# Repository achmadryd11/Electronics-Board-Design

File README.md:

# Electronics-Board-Design
PCB (Printed Circuit Board)

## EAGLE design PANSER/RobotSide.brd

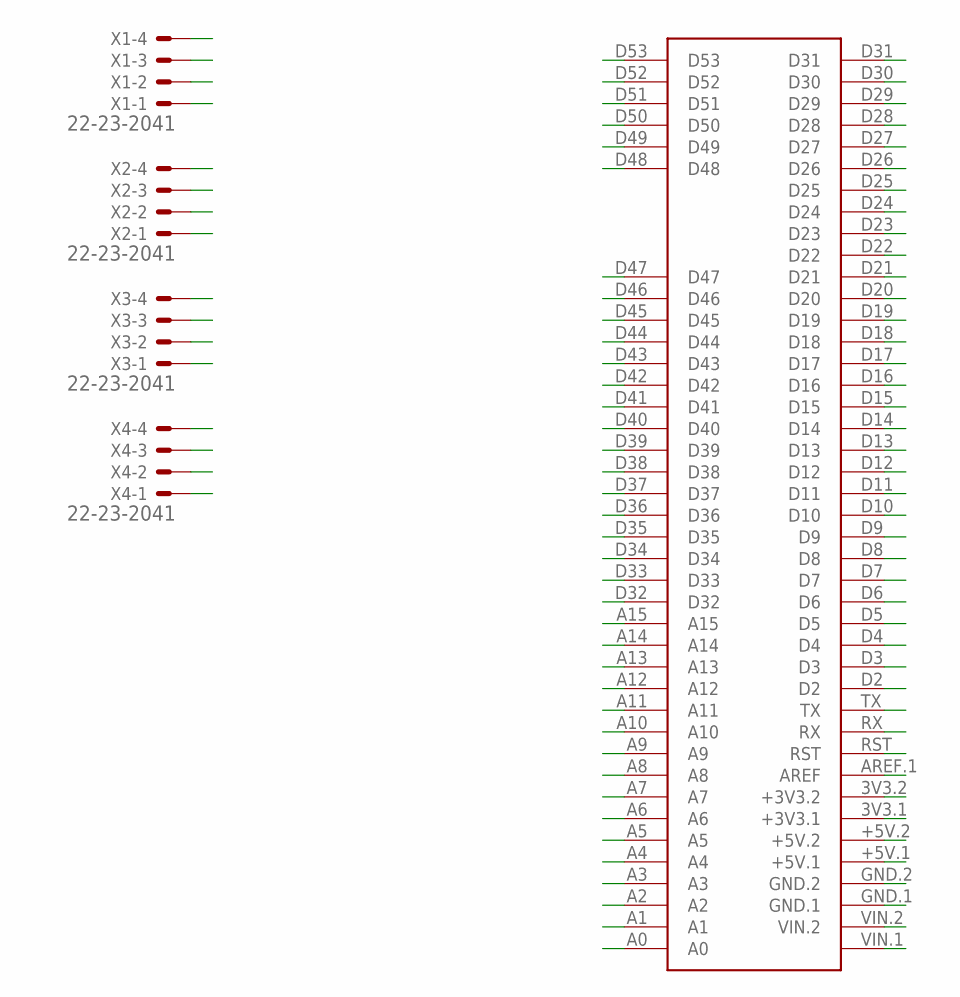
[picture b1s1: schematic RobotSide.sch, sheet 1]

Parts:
U$1: MEGA2560_MIKRO
X1, X2, X3, X4: 22-23-2041

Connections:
3V3: U$1.3V3.1 (+3V3.1), U$1.3V3.2 (+3V3.2)
5V: U$1.+5V.1, U$1.+5V.2; also elsewhere on the board
A0: U$1.A0
A1: U$1.A1
A2: U$1.A2
A3: U$1.A3
A4: U$1.A4
A5: U$1.A5
A6: U$1.A6
A7: U$1.A7
A8: U$1.A8
A9: U$1.A9
A10: U$1.A10
A11: U$1.A11
A12: U$1.A12
A13: U$1.A13
A14: U$1.A14
A15: U$1.A15
AREF: U$1.AREF.1 (AREF)
D2: U$1.D2
D3: U$1.D3
D4: U$1.D4
D5: U$1.D5
D6: U$1.D6
D7: U$1.D7
D8: U$1.D8
D9: U$1.D9
D10: U$1.D10
D11: U$1.D11
D12: U$1.D12
D13: U$1.D13
D14: U$1.D14
D15: U$1.D15
D16: U$1.D16
D17: U$1.D17
D18: U$1.D18
D19: U$1.D19
D20: U$1.D20
D21: U$1.D21
D22: U$1.D22
D23: U$1.D23
D24: U$1.D24
D25: U$1.D25
D26: U$1.D26
D27: U$1.D27
D28: U$1.D28
D29: U$1.D29
D30: U$1.D30
D31: U$1.D31
D32: U$1.D32
D33: U$1.D33
D34: U$1.D34
D35: U$1.D35
D36: U$1.D36
D37: U$1.D37
D38: U$1.D38
D39: U$1.D39
D40: U$1.D40
D41: U$1.D41
D42: U$1.D42
D43: U$1.D43
D44: U$1.D44
D45: U$1.D45
D46: U$1.D46
D47: U$1.D47
D49: U$1.D49
D50: U$1.D50
D51: U$1.D51
D52: U$1.D52
D53: U$1.D53
GND: U$1.GND.1, U$1.GND.2; also elsewhere on the board
RST: U$1.RST
RX0: U$1.RX
TX0: U$1.TX
VIN: U$1.VIN.1, U$1.VIN.2

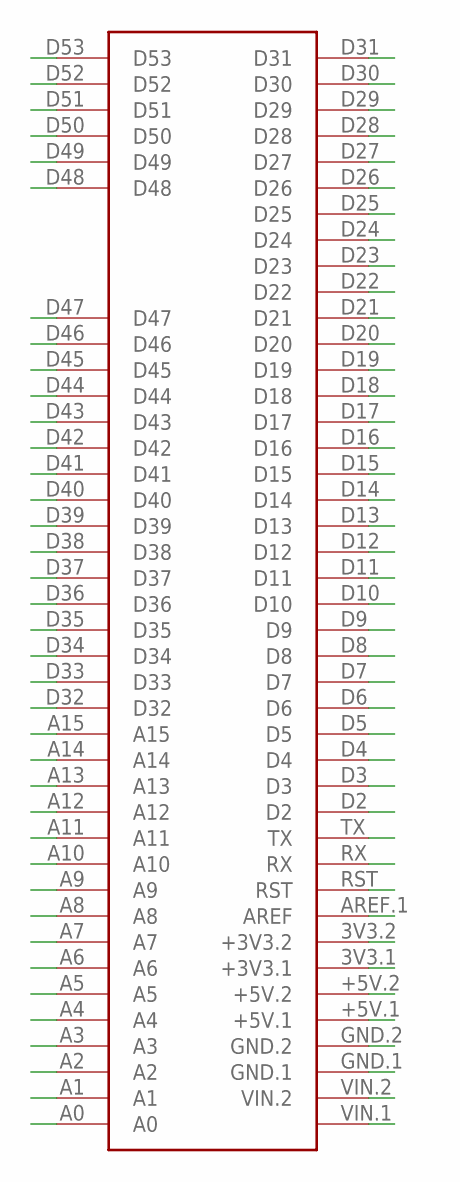
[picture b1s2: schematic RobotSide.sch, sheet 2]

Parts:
U$2: MEGA2560_MIKRO

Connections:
3V3_A: U$2.3V3.1 (+3V3.1), U$2.3V3.2 (+3V3.2)
5V: U$2.+5V.1, U$2.+5V.2; also elsewhere on the board
A0_A: U$2.A0
A1_A: U$2.A1
A2_A: U$2.A2
A3_A: U$2.A3
A4_A: U$2.A4
A5_A: U$2.A5
A6_A: U$2.A6
A7_A: U$2.A7
A8_A: U$2.A8
A9_A: U$2.A9
A10_A: U$2.A10
A11_A: U$2.A11
A12_A: U$2.A12
A13_A: U$2.A13
A14_A: U$2.A14
A15_A: U$2.A15
AREF_A: U$2.AREF.1 (AREF)
D2_A: U$2.D2
D3_A: U$2.D3
D4_A: U$2.D4
D5_A: U$2.D5
D6_A: U$2.D6
D7_A: U$2.D7
D8_A: U$2.D8
D9_A: U$2.D9
D10_A: U$2.D10
D11_A: U$2.D11
D12_A: U$2.D12
D13_A: U$2.D13
D14_A: U$2.D14
D15_A: U$2.D15
D16_A: U$2.D16
D17_A: U$2.D17
D18_A: U$2.D18
D19_A: U$2.D19
D20_A: U$2.D20
D21_A: U$2.D21
D22_A: U$2.D22
D23_A: U$2.D23
D24_A: U$2.D24
D25_A: U$2.D25
D26_A: U$2.D26
D27_A: U$2.D27
D28_A: U$2.D28
D29_A: U$2.D29
D30_A: U$2.D30
D31_A: U$2.D31
D32_A: U$2.D32
D33_A: U$2.D33
D34_A: U$2.D34
D35_A: U$2.D35
D36_A: U$2.D36
D37_A: U$2.D37
D38_A: U$2.D38
D39_A: U$2.D39
D40_A: U$2.D40
D41_A: U$2.D41
D42_A: U$2.D42
D43_A: U$2.D43
D44_A: U$2.D44
D45_A: U$2.D45
D46_A: U$2.D46
D47_A: U$2.D47
D48_A: U$2.D48
D49_A: U$2.D49
D50_A: U$2.D50
D51_A: U$2.D51
D52_A: U$2.D52
D53_A: U$2.D53
GND: U$2.GND.1, U$2.GND.2; also elsewhere on the board
RST_A: U$2.RST
RX0_A: U$2.RX
TX0_A: U$2.TX
VIN_A: U$2.VIN.1, U$2.VIN.2

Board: 2 copper layers, 6 parts (0 on the bottom side), 6 nets, no tracks yet.

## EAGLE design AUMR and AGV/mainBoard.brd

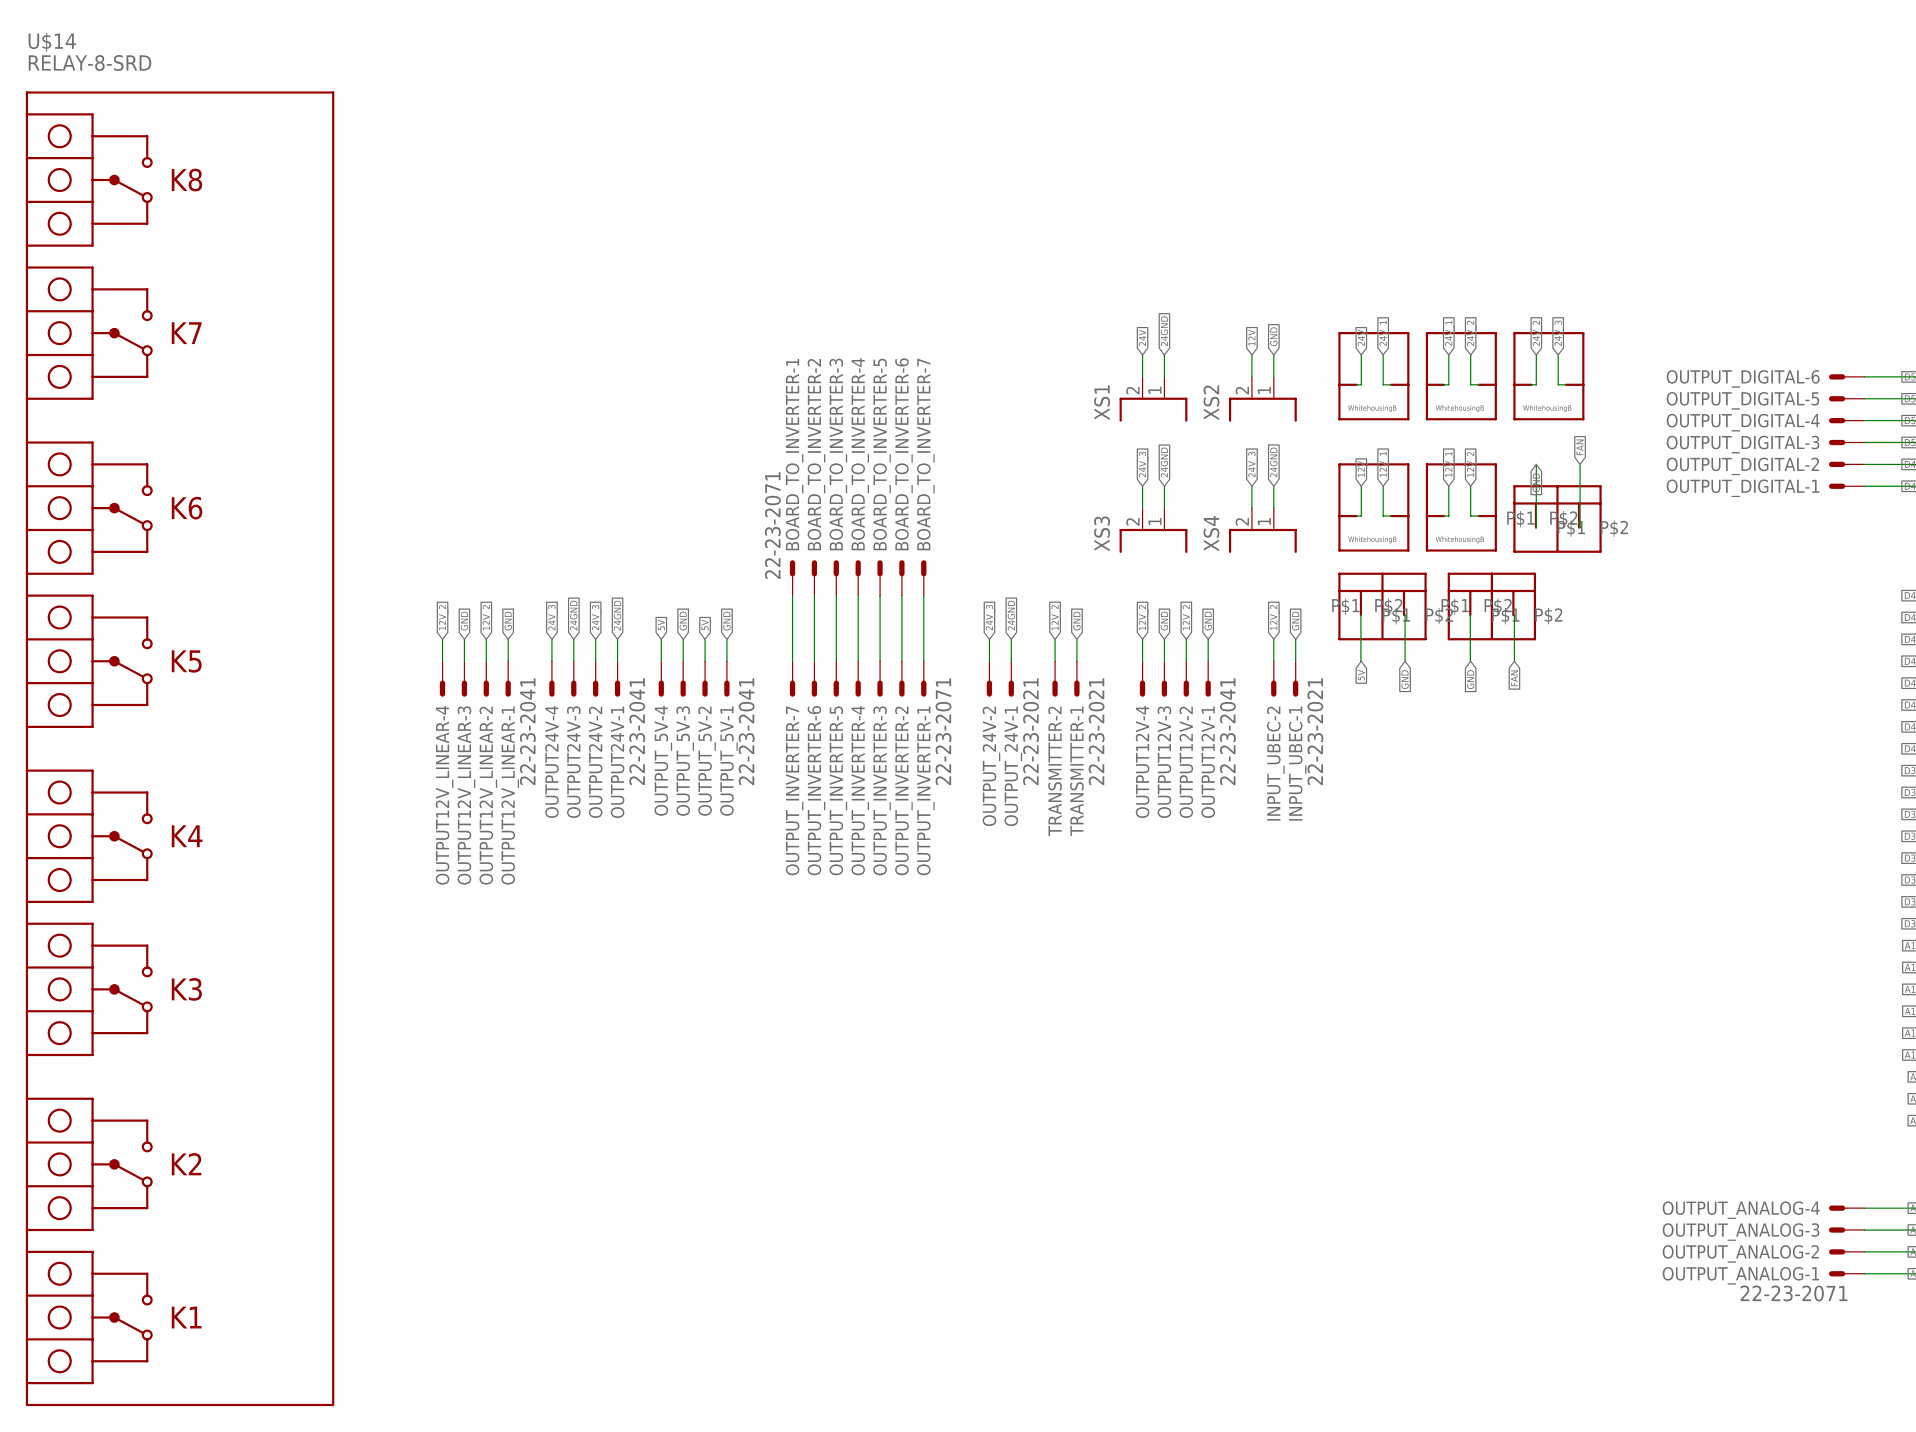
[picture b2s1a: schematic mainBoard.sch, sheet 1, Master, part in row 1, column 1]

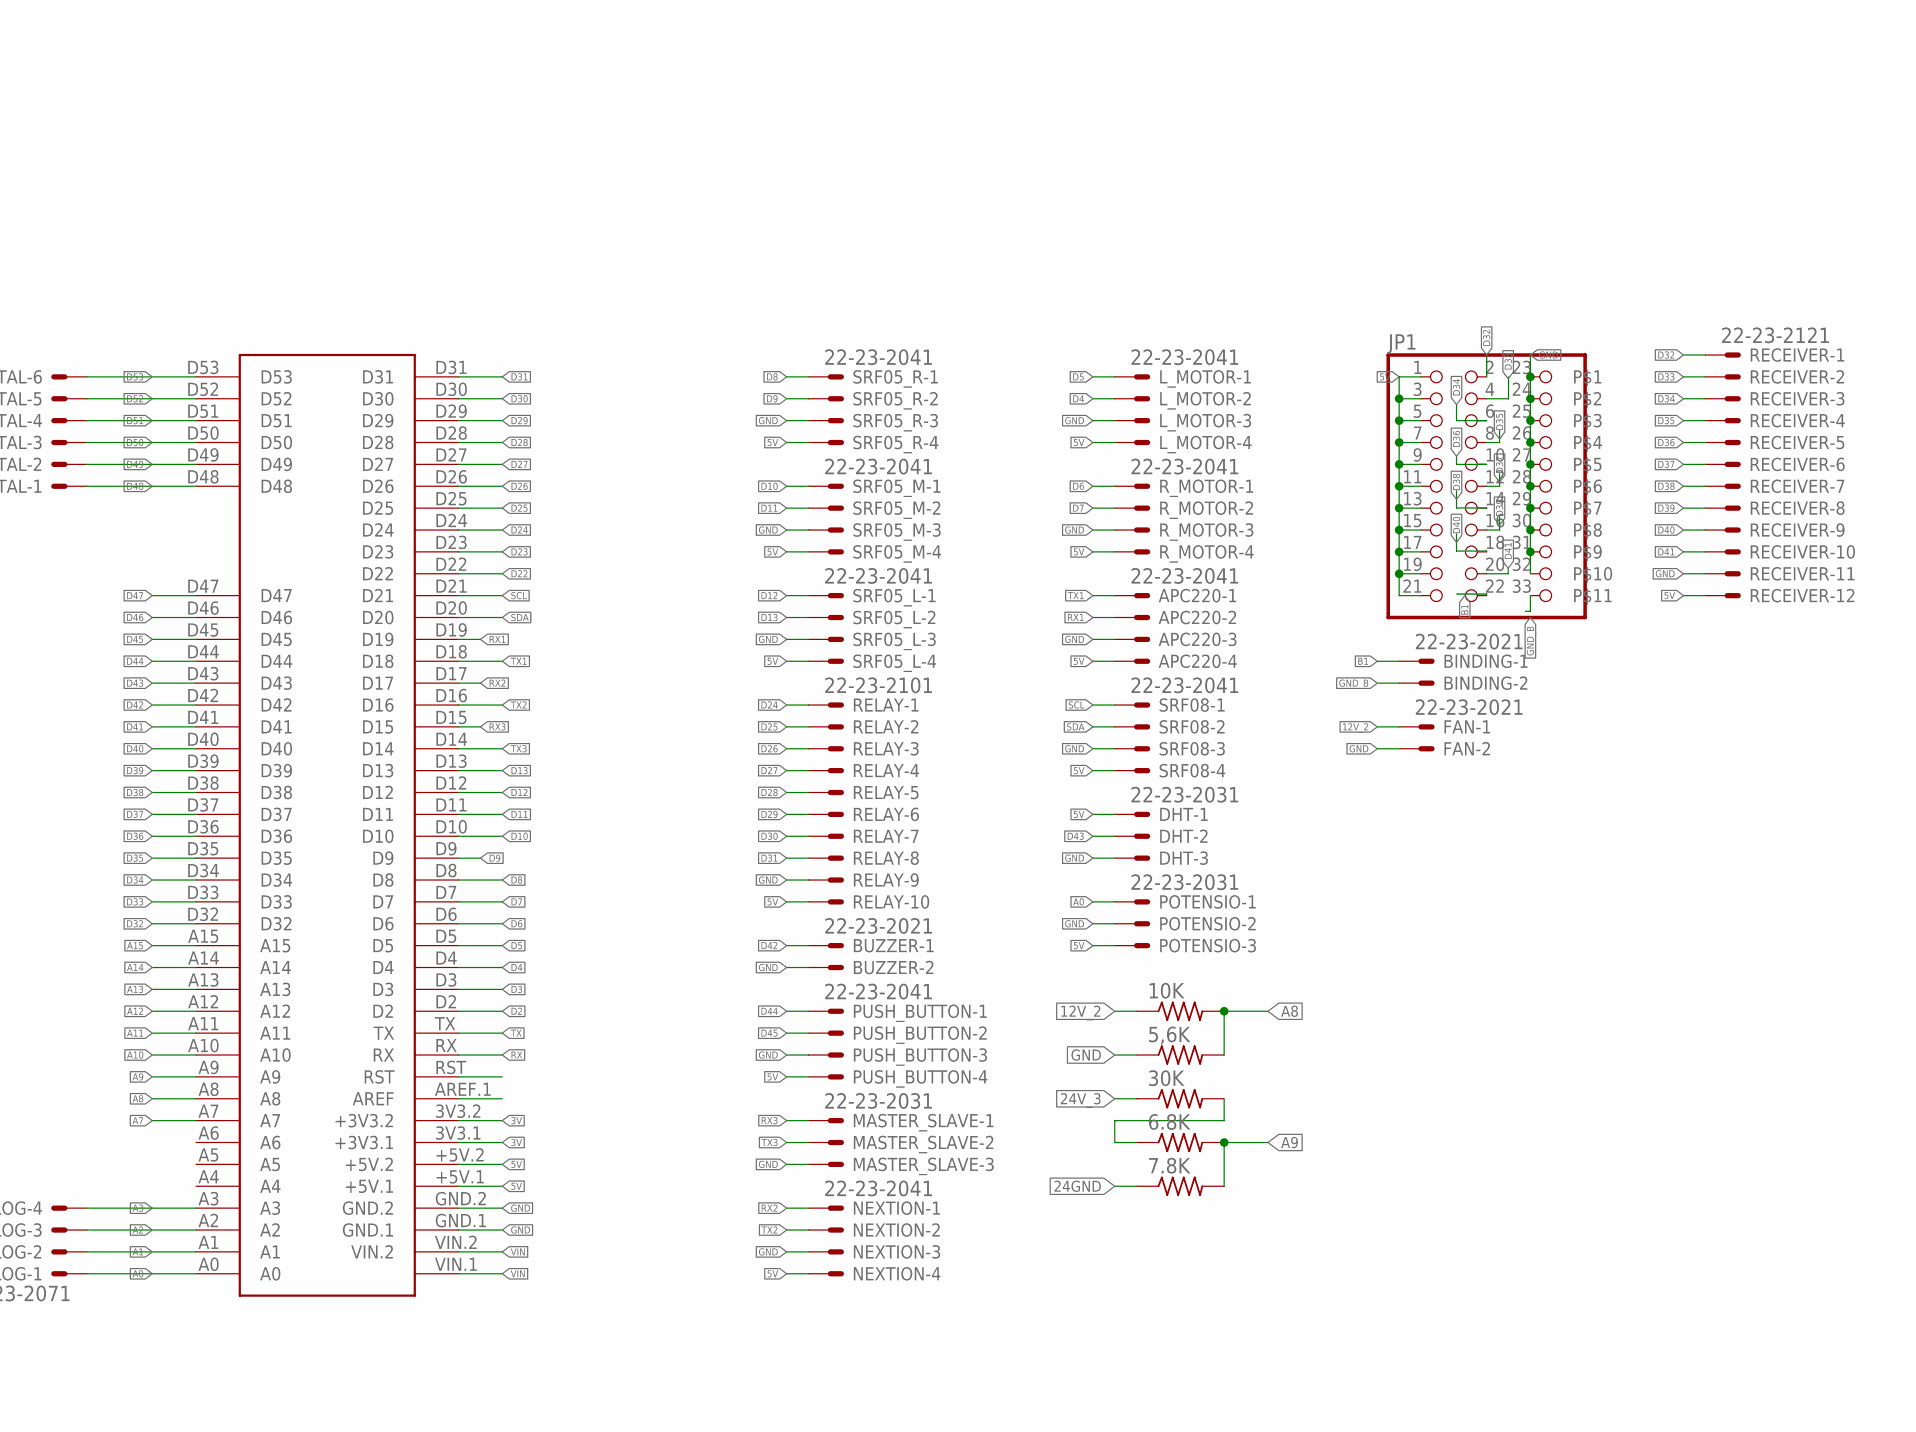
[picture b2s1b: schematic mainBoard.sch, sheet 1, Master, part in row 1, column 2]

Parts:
5,6K, 6.8K, 7.8K, 10K, 30K: R-US_0207/7; 0207/7
APC220: 22-23-2041
BINDING: 22-23-2021
BOARD_TO_INVERTER: 22-23-2071
BUZZER: 22-23-2021
DHT: 22-23-2031
EMERGENCY: WHB
FAN: 22-23-2021
FANLEFT: TERMINALBLOCK5MM
FANRIGHT: TERMINALBLOCK5MM
FUSE12V, FUSE24V: WHB
INPUT_UBEC: 22-23-2021
JP1: PINHD-2X11; 2X11
L_MOTOR: 22-23-2041
MASTER_SLAVE: 22-23-2031
NEXTION: 22-23-2041
OUTPUT12V, OUTPUT12V_LINEAR, OUTPUT24V: 22-23-2041
OUTPUT_5V: 22-23-2041
OUTPUT_24V: 22-23-2021
OUTPUT_ANALOG: 22-23-2071
OUTPUT_DIGITAL: 22-23-2061
OUTPUT_INVERTER: 22-23-2071
POTENSIO: 22-23-2031
PUSH_BUTTON: 22-23-2041
RECEIVER: 22-23-2121
RELAY: 22-23-2101
R_MOTOR: 22-23-2041
SRF05_L, SRF05_M, SRF05_R, SRF08: 22-23-2041
SWITCH24V: WHB
SWTICH12V: WHB
TRANSMITTER: 22-23-2021
U$1: MEGA2560_MIKRO
U$14: RELAY-8-SRD
UBEC_OUTPUT: TERMINALBLOCK5MM
XS1, XS2, XS3, XS4: 2P; DG55CB-2P-1

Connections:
3V: U$1.3V3.1 (+3V3.1), U$1.3V3.2 (+3V3.2); also elsewhere on the board
5V: APC220.4, DHT.1, JP1.1, JP1.3, JP1.5, JP1.7, JP1.9, JP1.11, JP1.13, JP1.15, JP1.17, JP1.19, JP1.21, L_MOTOR.4, NEXTION.4, OUTPUT_5V.2, OUTPUT_5V.4, POTENSIO.3, PUSH_BUTTON.4, RECEIVER.12, RELAY.10, R_MOTOR.4, SRF05_L.4, SRF05_M.4, SRF05_R.4, SRF08.4, U$1.+5V.1, U$1.+5V.2, UBEC_OUTPUT.P$1; also elsewhere on the board
12V: FUSE12V.P$1, XS2.2
12V_1: FUSE12V.P$2, SWTICH12V.P$1
12V_2: 10K.1, FAN.1, INPUT_UBEC.2, OUTPUT12V.2, OUTPUT12V.4, OUTPUT12V_LINEAR.2, OUTPUT12V_LINEAR.4, SWTICH12V.P$2, TRANSMITTER.2; also elsewhere on the board
24GND: 7.8K.1, OUTPUT24V.1, OUTPUT24V.3, OUTPUT_24V.1, XS1.1, XS3.1, XS4.1
24V: FUSE24V.P$1, XS1.2
24V_1: FUSE24V.P$2, SWITCH24V.P$1
24V_2: EMERGENCY.P$1, SWITCH24V.P$2
24V_3: 30K.1, EMERGENCY.P$2, OUTPUT24V.2, OUTPUT24V.4, OUTPUT_24V.2, XS3.2, XS4.2
A0: OUTPUT_ANALOG.1, POTENSIO.1, U$1.A0
A1: OUTPUT_ANALOG.2, U$1.A1
A2: OUTPUT_ANALOG.3, U$1.A2
A3: OUTPUT_ANALOG.4, U$1.A3
A7: U$1.A7
A8: 5,6K.2, 10K.2, U$1.A8
A9: 6.8K.2, 7.8K.2, U$1.A9
A10: U$1.A10
A11: U$1.A11
A12: U$1.A12
A13: U$1.A13
A14: U$1.A14
A15: U$1.A15
B1: BINDING.1, JP1.22
D2: U$1.D2
D3: U$1.D3
D4: L_MOTOR.2, U$1.D4
D5: L_MOTOR.1, U$1.D5
D6: R_MOTOR.1, U$1.D6
D7: R_MOTOR.2, U$1.D7
D8: SRF05_R.1, U$1.D8
D9: SRF05_R.2, U$1.D9
D10: SRF05_M.1, U$1.D10
D11: SRF05_M.2, U$1.D11
D12: SRF05_L.1, U$1.D12
D13: SRF05_L.2, U$1.D13
D22: U$1.D22
D23: U$1.D23
D24: RELAY.1, U$1.D24
D25: RELAY.2, U$1.D25
D26: RELAY.3, U$1.D26
D27: RELAY.4, U$1.D27
D28: RELAY.5, U$1.D28
D29: RELAY.6, U$1.D29
D30: RELAY.7, U$1.D30
D31: RELAY.8, U$1.D31
D32: JP1.2, RECEIVER.1, U$1.D32
D33: JP1.4, RECEIVER.2, U$1.D33
D34: JP1.6, RECEIVER.3, U$1.D34
D35: JP1.8, RECEIVER.4, U$1.D35
D36: JP1.10, RECEIVER.5, U$1.D36
D37: JP1.12, RECEIVER.6, U$1.D37
D38: JP1.14, RECEIVER.7, U$1.D38
D39: JP1.16, RECEIVER.8, U$1.D39
D40: JP1.18, RECEIVER.9, U$1.D40
D41: JP1.20, RECEIVER.10, U$1.D41
D42: BUZZER.1, U$1.D42
D43: DHT.2, U$1.D43
D44: PUSH_BUTTON.1, U$1.D44
D45: PUSH_BUTTON.2, U$1.D45
D46: U$1.D46
D47: U$1.D47
D48: OUTPUT_DIGITAL.1, U$1.D48
D49: OUTPUT_DIGITAL.2, U$1.D49
D50: OUTPUT_DIGITAL.3, U$1.D50
D51: OUTPUT_DIGITAL.4, U$1.D51
D52: OUTPUT_DIGITAL.5, U$1.D52
D53: OUTPUT_DIGITAL.6, U$1.D53
FAN: FANLEFT.P$2, FANRIGHT.P$2
GND: 5,6K.1, APC220.3, BUZZER.2, DHT.3, FAN.2, FANLEFT.P$1, FANRIGHT.P$1, INPUT_UBEC.1, JP1.23, JP1.24, JP1.25, JP1.26, JP1.27, JP1.28, JP1.29, JP1.30, JP1.31, JP1.32, L_MOTOR.3, MASTER_SLAVE.3, NEXTION.3, OUTPUT12V.1, OUTPUT12V.3, OUTPUT12V_LINEAR.1, OUTPUT12V_LINEAR.3, OUTPUT_5V.1, OUTPUT_5V.3, POTENSIO.2, PUSH_BUTTON.3, RECEIVER.11, RELAY.9, R_MOTOR.3, SRF05_L.3, SRF05_M.3, SRF05_R.3, SRF08.3, TRANSMITTER.1, U$1.GND.1, U$1.GND.2, UBEC_OUTPUT.P$2, XS2.1; also elsewhere on the board
GND_B: BINDING.2, JP1.33
unnamed: 6.8K.1, 30K.2
unnamed: BOARD_TO_INVERTER.1, OUTPUT_INVERTER.7
unnamed: BOARD_TO_INVERTER.2, OUTPUT_INVERTER.6
unnamed: BOARD_TO_INVERTER.3, OUTPUT_INVERTER.5
unnamed: BOARD_TO_INVERTER.4, OUTPUT_INVERTER.4
unnamed: BOARD_TO_INVERTER.5, OUTPUT_INVERTER.3
unnamed: BOARD_TO_INVERTER.6, OUTPUT_INVERTER.2
unnamed: BOARD_TO_INVERTER.7, OUTPUT_INVERTER.1
RX: U$1.RX
RX1: APC220.2, U$1.D19
RX2: NEXTION.1, U$1.D17
RX3: MASTER_SLAVE.1, U$1.D15; also elsewhere on the board
SCL: SRF08.1, U$1.D21
SDA: SRF08.2, U$1.D20
TX: U$1.TX
TX1: APC220.1, U$1.D18
TX2: NEXTION.2, U$1.D16
TX3: MASTER_SLAVE.2, U$1.D14; also elsewhere on the board
VIN: U$1.VIN.1, U$1.VIN.2; also elsewhere on the board

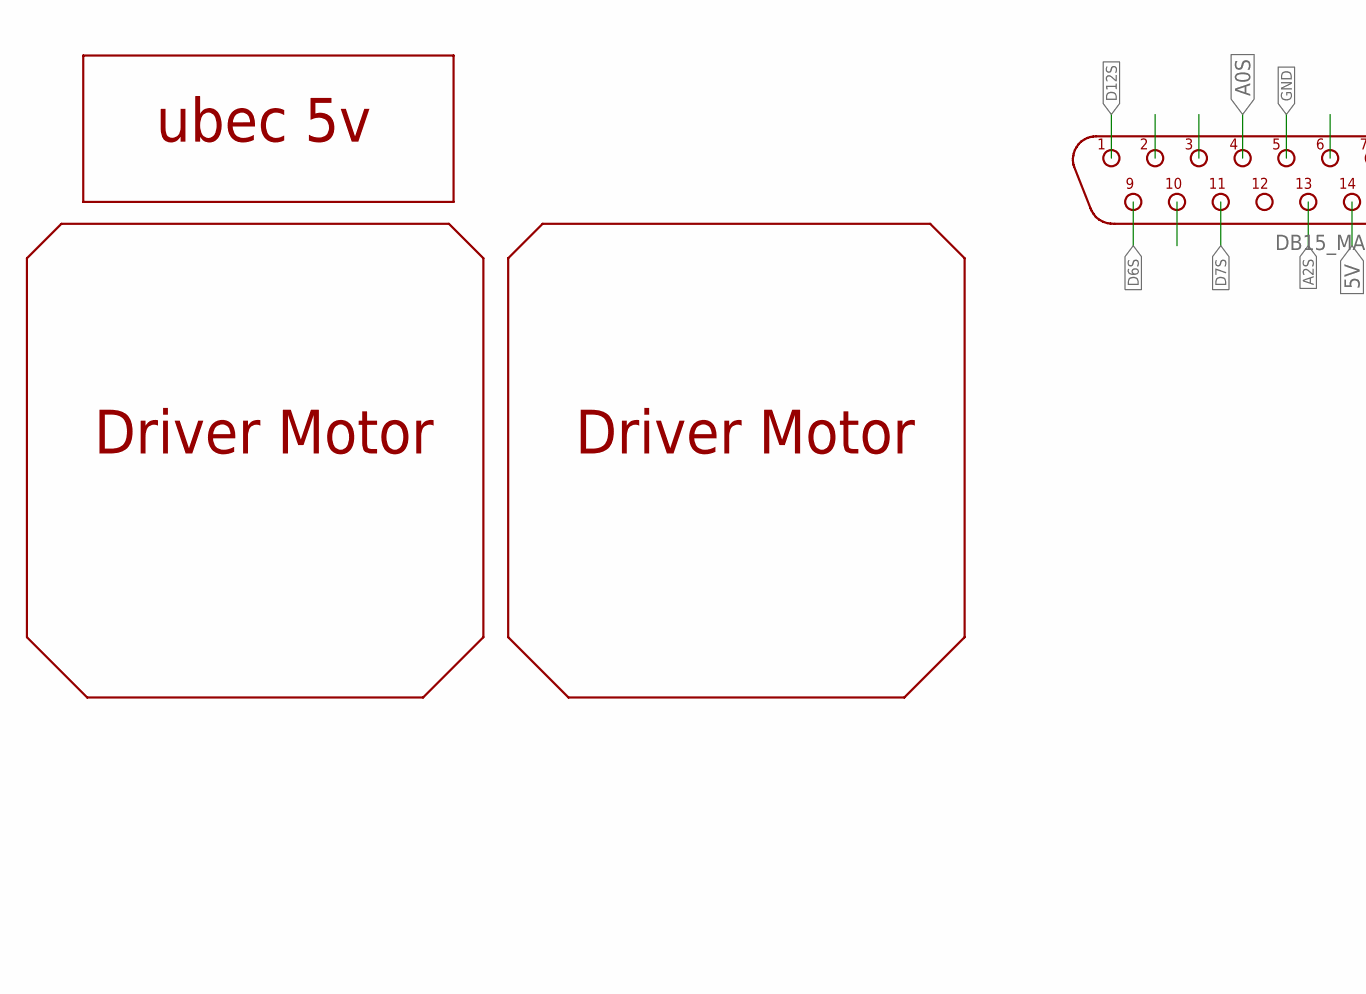
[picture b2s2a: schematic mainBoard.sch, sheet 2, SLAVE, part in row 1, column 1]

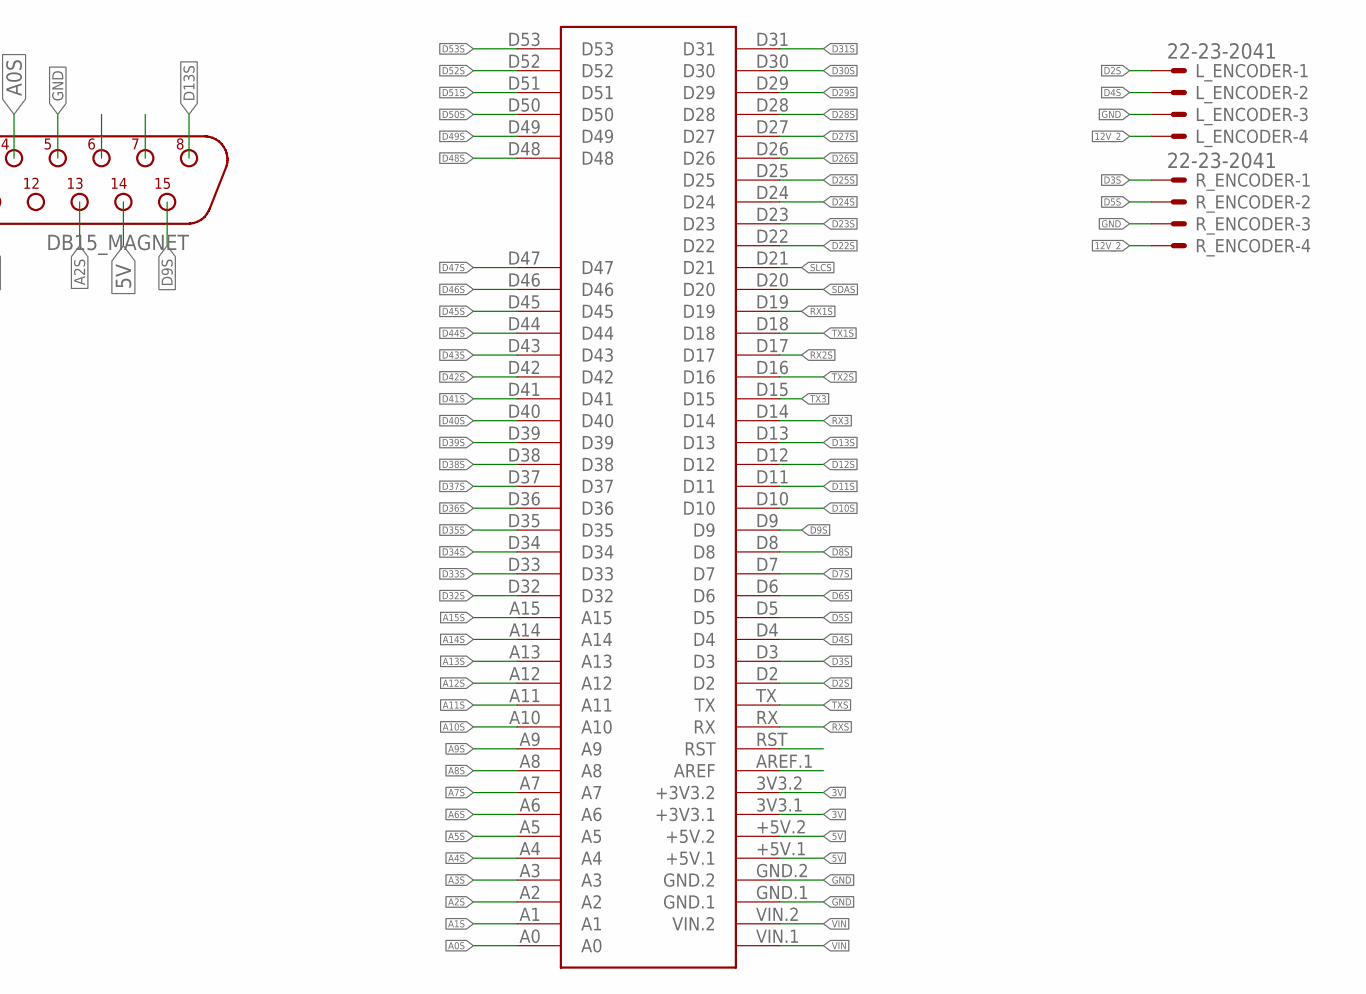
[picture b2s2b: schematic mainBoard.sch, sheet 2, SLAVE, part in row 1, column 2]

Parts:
DB15_MAGNET: DB15M/90; D-15M/90
L_ENCODER: 22-23-2041
R_ENCODER: 22-23-2041
U$2: MEGA2560_MIKRO
U$11, U$12: BT2; IBT2
U$13: UBEC; AD

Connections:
3V: U$2.3V3.1 (+3V3.1), U$2.3V3.2 (+3V3.2); also elsewhere on the board
5V: DB15_MAGNET.14, U$2.+5V.1, U$2.+5V.2; also elsewhere on the board
12V_2: L_ENCODER.4, R_ENCODER.4; also elsewhere on the board
A0S: DB15_MAGNET.4, U$2.A0
A1S: U$2.A1
A2S: DB15_MAGNET.13, U$2.A2
A3S: U$2.A3
A4S: U$2.A4
A5S: U$2.A5
A6S: U$2.A6
A7S: U$2.A7
A8S: U$2.A8
A9S: U$2.A9
A10S: U$2.A10
A11S: U$2.A11
A12S: U$2.A12
A13S: U$2.A13
A14S: U$2.A14
A15S: U$2.A15
D2S: L_ENCODER.1, U$2.D2
D3S: R_ENCODER.1, U$2.D3
D4S: L_ENCODER.2, U$2.D4
D5S: R_ENCODER.2, U$2.D5
D6S: DB15_MAGNET.9, U$2.D6
D7S: DB15_MAGNET.11, U$2.D7
D8S: U$2.D8
D9S: DB15_MAGNET.15, U$2.D9
D10S: U$2.D10
D11S: U$2.D11
D12S: DB15_MAGNET.1, U$2.D12
D13S: DB15_MAGNET.8, U$2.D13
D22S: U$2.D22
D23S: U$2.D23
D24S: U$2.D24
D25S: U$2.D25
D26S: U$2.D26
D27S: U$2.D27
D28S: U$2.D28
D29S: U$2.D29
D30S: U$2.D30
D31S: U$2.D31
D32S: U$2.D32
D33S: U$2.D33
D34S: U$2.D34
D35S: U$2.D35
D36S: U$2.D36
D37S: U$2.D37
D38S: U$2.D38
D39S: U$2.D39
D40S: U$2.D40
D41S: U$2.D41
D42S: U$2.D42
D43S: U$2.D43
D44S: U$2.D44
D45S: U$2.D45
D46S: U$2.D46
D47S: U$2.D47
D48S: U$2.D48
D49S: U$2.D49
D50S: U$2.D50
D51S: U$2.D51
D52S: U$2.D52
D53S: U$2.D53
GND: DB15_MAGNET.5, L_ENCODER.3, R_ENCODER.3, U$2.GND.1, U$2.GND.2; also elsewhere on the board
RX1S: U$2.D19
RX2S: U$2.D17
RX3: U$2.D14; also elsewhere on the board
RXS: U$2.RX
SDAS: U$2.D20
SLCS: U$2.D21
TX1S: U$2.D18
TX2S: U$2.D16
TX3: U$2.D15; also elsewhere on the board
TXS: U$2.TX
VIN: U$2.VIN.1, U$2.VIN.2; also elsewhere on the board

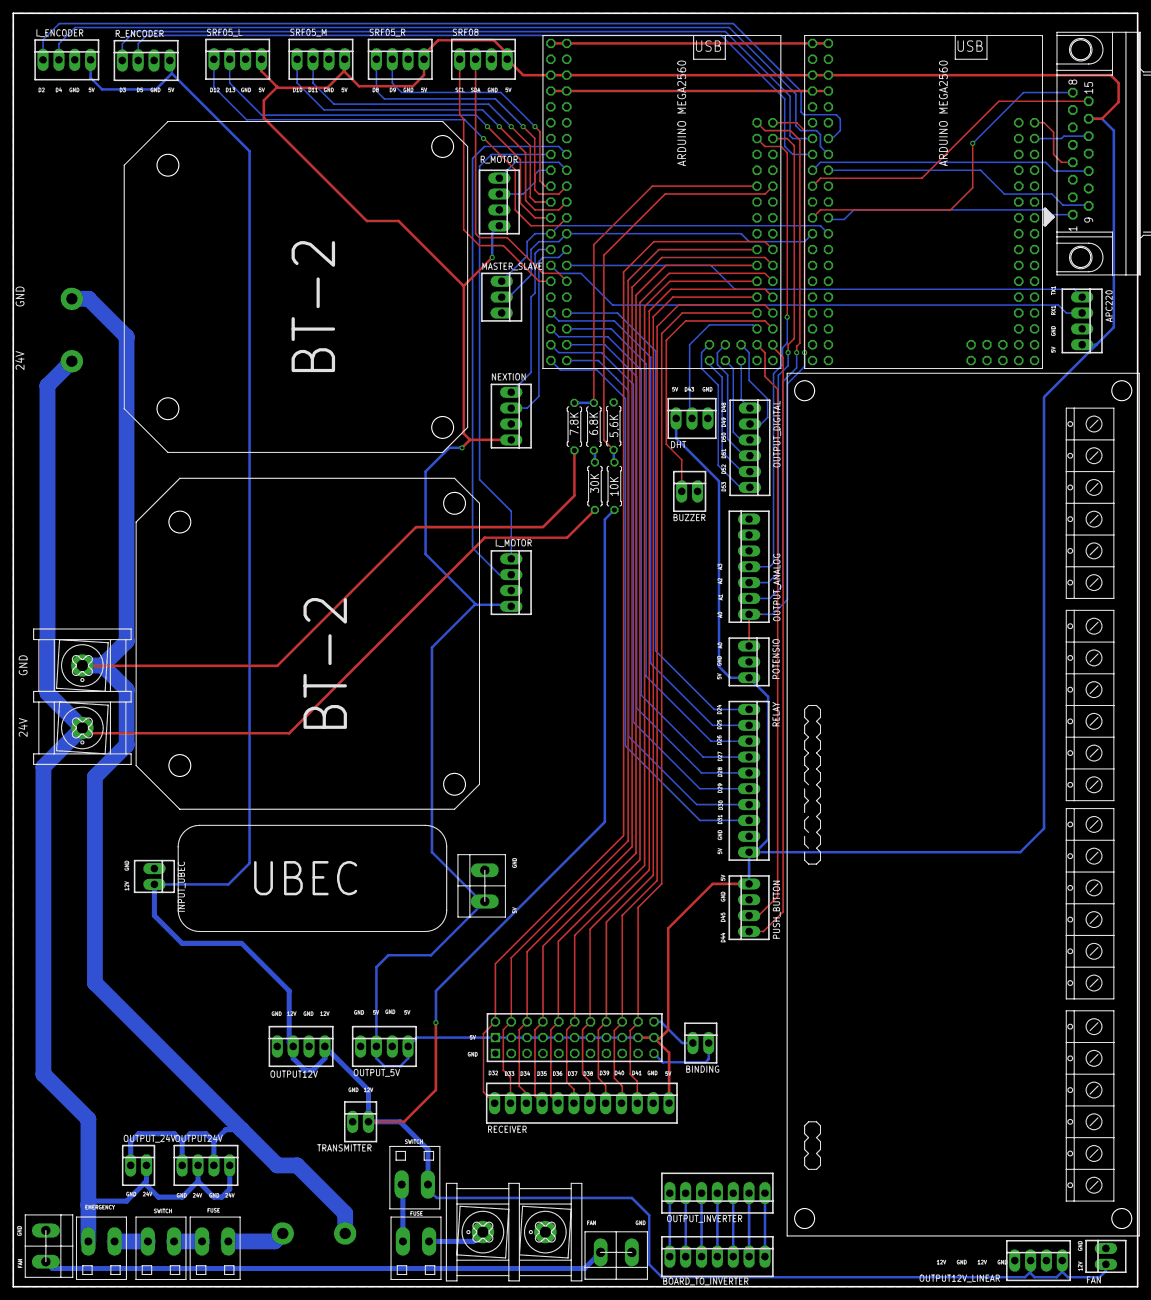
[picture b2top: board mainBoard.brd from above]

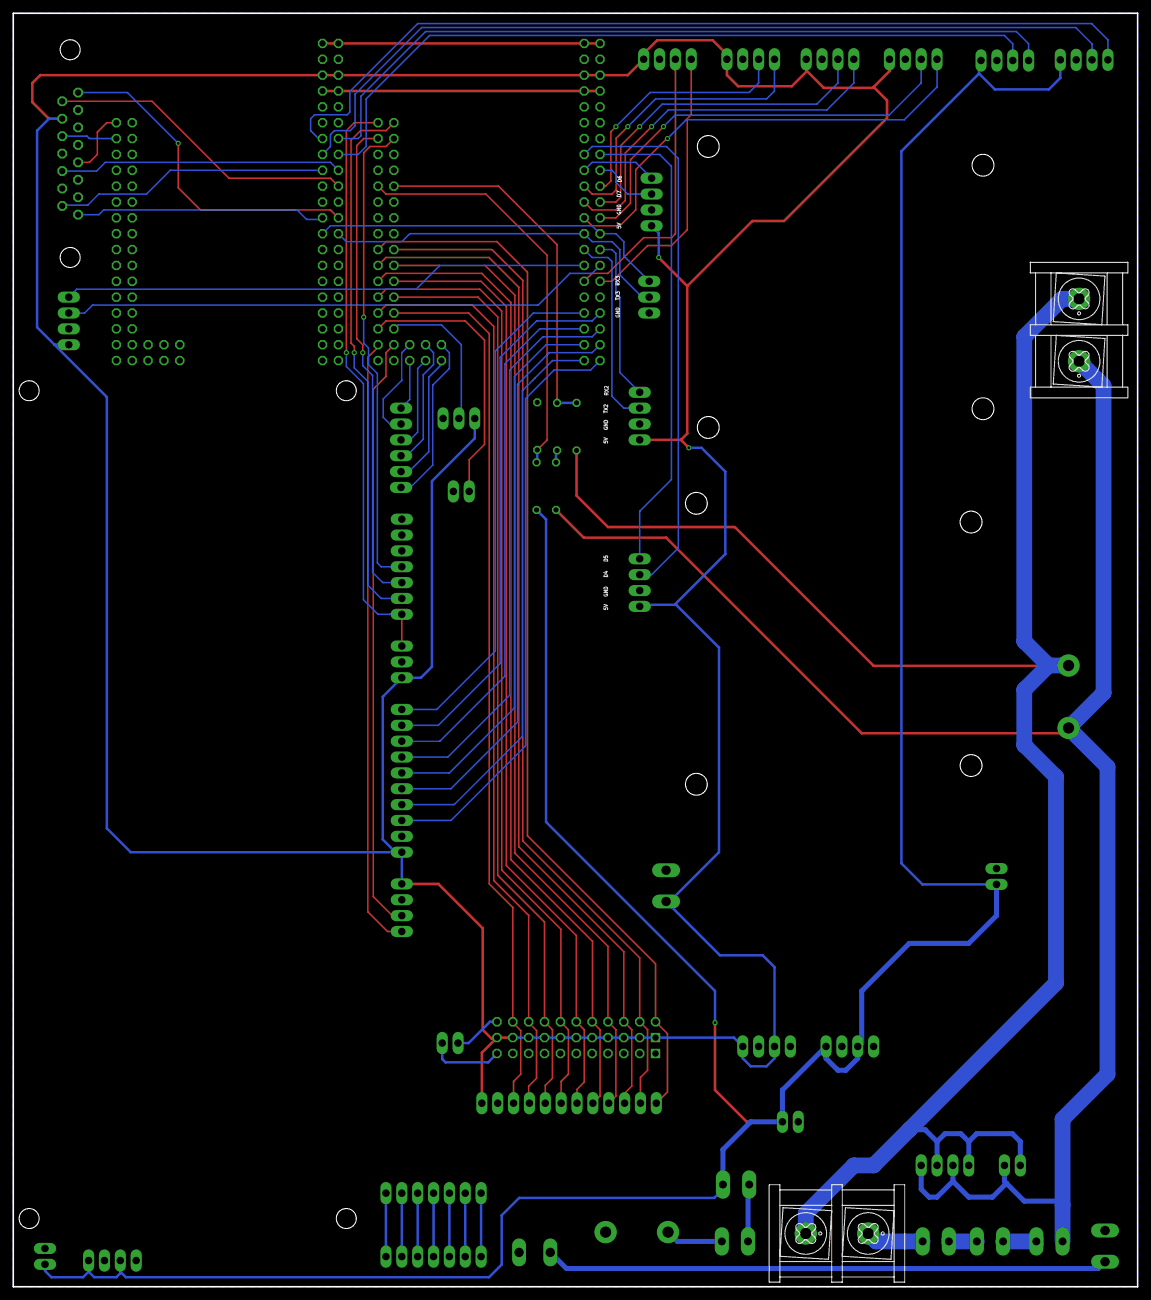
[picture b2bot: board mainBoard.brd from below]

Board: 2 copper layers, 180.1 x 204.0 mm, 55 parts (2 on the bottom side), 86 nets.

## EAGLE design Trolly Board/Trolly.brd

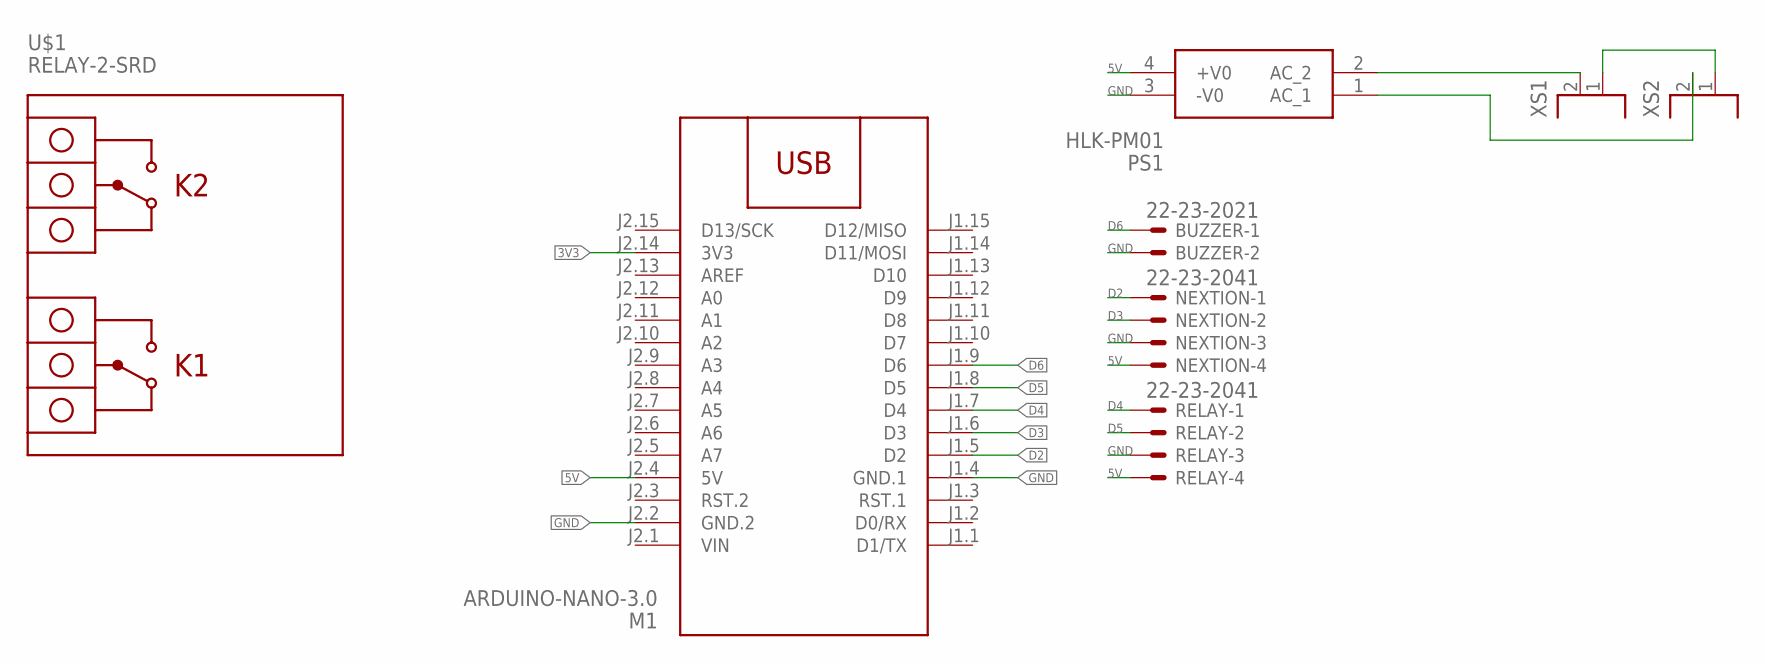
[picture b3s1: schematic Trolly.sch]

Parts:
BUZZER: 22-23-2021
M1: ARDUINO-NANO-3.0
NEXTION: 22-23-2041
PS1: HLK-PM01; HLKPM01
RELAY: 22-23-2041
U$1: RELAY-2-SRD
XS1, XS2: 2P; DG55CB-2P-1

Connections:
3V3: M1.J2.14 (3V3)
5V: M1.J2.4 (5V), NEXTION.4, PS1.4 (+V0), RELAY.4
D2: M1.J1.5 (D2), NEXTION.1
D3: M1.J1.6 (D3), NEXTION.2
D4: M1.J1.7 (D4), RELAY.1
D5: M1.J1.8 (D5), RELAY.2
D6: BUZZER.1, M1.J1.9 (D6)
GND: BUZZER.2, M1.J1.4 (GND.1), M1.J2.2 (GND.2), NEXTION.3, PS1.3 (-V0), RELAY.3
unnamed: XS1.1, XS2.1
unnamed: PS1.1 (AC_1), XS2.2
unnamed: PS1.2 (AC_2), XS1.2
VIN: M1.J2.1 (VIN)

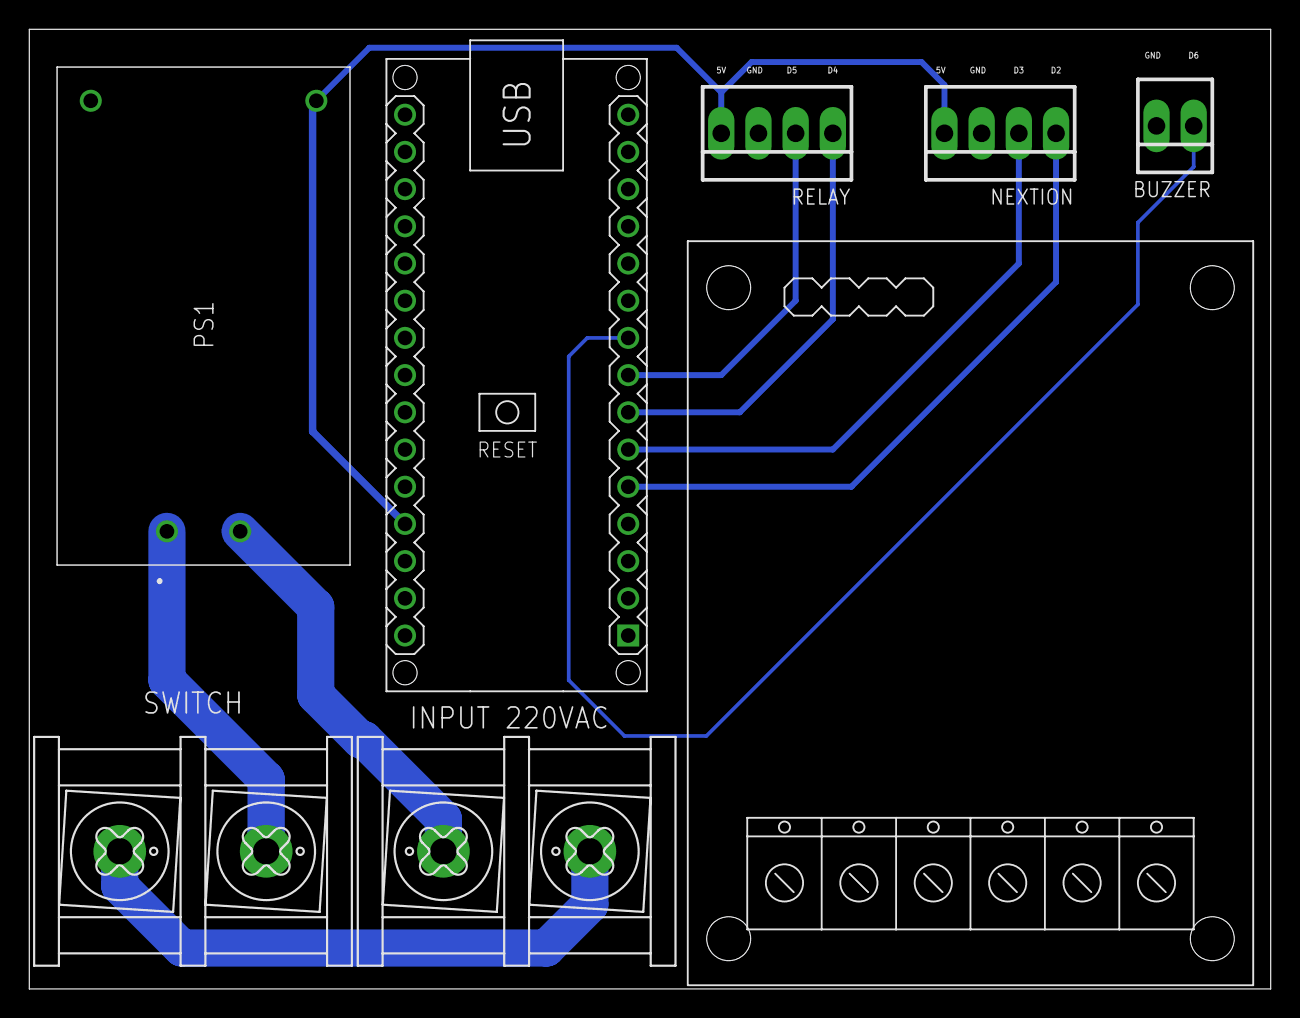
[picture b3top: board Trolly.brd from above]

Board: 2 copper layers, 84.8 x 65.5 mm, 8 parts (0 on the bottom side), 10 nets.

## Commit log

2021-07-11 Printed Circuit Board
2021-09-24 update panser board

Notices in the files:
parts and their libraries:
diy-modules: Released under the Creative Commons Attribution 4.0 International License: http://creativecommons.org/licenses/by/4.0
